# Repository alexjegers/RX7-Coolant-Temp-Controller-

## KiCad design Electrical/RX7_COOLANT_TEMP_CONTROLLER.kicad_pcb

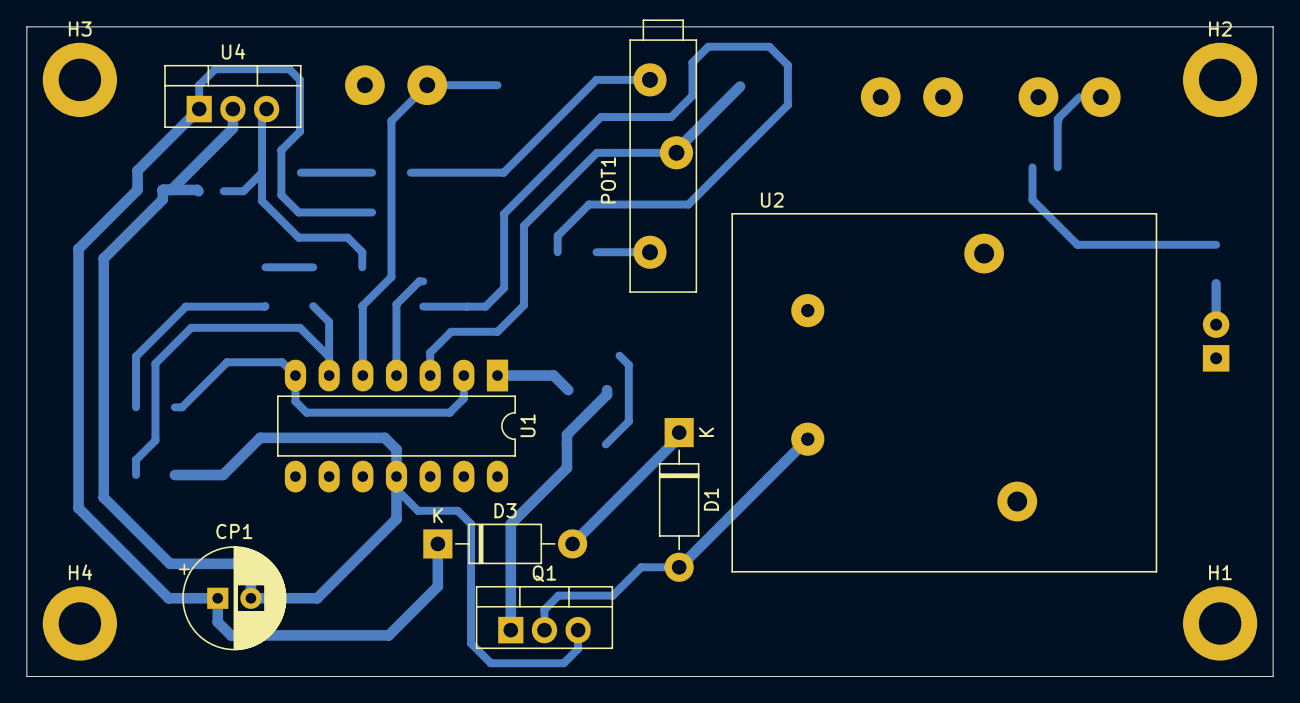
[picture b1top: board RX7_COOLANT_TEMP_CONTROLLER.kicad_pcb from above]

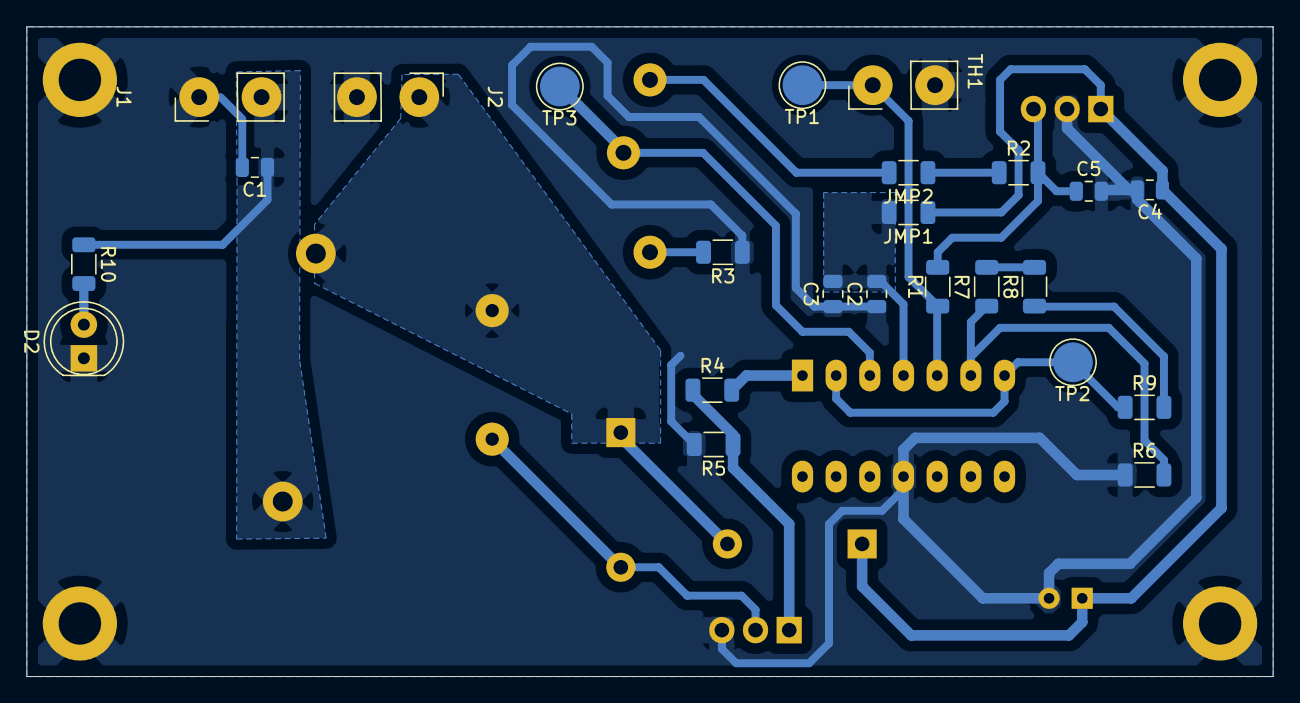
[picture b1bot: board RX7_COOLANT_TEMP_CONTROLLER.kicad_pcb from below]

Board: 2 copper layers, 94.0 x 49.0 mm, 36 parts (24 on the bottom side), 17 nets.

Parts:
C1, C3: 100n; C_0805_2012Metric
C2: .1u; C_0805_2012Metric
C4, C5: 22u; C_0805_2012Metric
CP1: 470u; CP_Radial_D7.5mm_P2.50mm
D1, D3: 1N1589; D_DO-41_SOD81_P10.16mm_Horizontal
D2: LED; LED_D5.0mm
H1, H2, H3, H4: MountingHole_Pad; MountingHole_3.2mm_M3_DIN965_Pad
J1: Fan Connector; RX-7_COOLANT_TEMP_2_PIN_CONN
J2: +12V Connector; RX-7_COOLANT_TEMP_2_PIN_CONN
JMP1, JMP2: 0; R_1206_3216Metric
POT1: 10k; 20K_RECT_POT
Q1: IRLZ44N; TO-220-3_Vertical
R1: 330; R_1206_3216Metric
R2: 10k; R_1206_3216Metric
R3: 5.1k; R_1206_3216Metric
R4: 200; R_1206_3216Metric
R5: 47K; R_1206_3216Metric
R6, R9: 1k; R_1206_3216Metric
R7: 51; R_1206_3216Metric
R8, R10: 750; R_1206_3216Metric
TH1: Coolant Temp Sensor; RX-7_COOLANT_TEMP_2_PIN_CONN
TP1: Vout; TestPoint_Pad_D3.0mm
TP2: Vout_gain; TestPoint_Pad_D3.0mm
TP3: Vref; TestPoint_Pad_D3.0mm
U1: LM324; DIP-14_W7.62mm_LongPads
U2: AZ2100_1A_12DEF
U4: LM7805_TO220; TO-220-3_Vertical

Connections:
+5V: C5.1, R1.1, R2.2, U4.3
+12V: D1.1, D3.2, J2.1, U2.1, U2.3
/FAN_POS: C1.1, J1.2, R10.1, U2.4
/FB_IN: R9.1, TP2.1, U1.2, U1.7
/FB_OUT: R6.2, R7.2, U1.6
/GDR: Q1.1, R4.1, R5.1
/LB: POT1.1, R3.2
/SENS_VOUT: R1.2, TH1.1, TP1.1, U1.5
/UB: JMP2.1, JMP2.2, POT1.3, R2.1
/VREF: POT1.2, TP3.1, U1.3
GND: C1.2, C2.1, C3.1, C4.2, C5.2, CP1.2, D2.1, H1.1, H2.1, H3.1, H4.1, J1.1, J2.2, Q1.3, R3.1, R5.2, R6.1, TH1.2, U1.11, U4.2
unnamed: D1.2, Q1.2, U2.2
unnamed: D2.2, R10.2
unnamed: R4.2, U1.1
unnamed: R7.1, R8.2
unnamed: R8.1, R9.2
V_DIODE: C2.2, C3.2, C4.1, CP1.1, D3.1, JMP1.1, JMP1.2, U1.4, U4.1
